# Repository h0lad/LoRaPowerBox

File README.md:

## What is this thing?

This PCB integrates a Heltec HT-CT62 (ESP32-C3 + SX1262), a TI BQ25628E wide-range Li-ion charger and a TI TPS631000 buck-boost converter providing a stable 3.3V rail at up to 1.5A. The TI BQ25628E is capable of handling highly dynamic sources like solar cells and wind generators.

## Features

- 3.9-18V input range, with survival up to 26 V  
- Up to 3.2A input current (IBUS)  
- Up to 2A battery charge current (IBAT)  
- Up to 3.5A system output current (ISW), limited to 1.5A @ 3.3V by the TPS631000  
- Configurable hot/cold charging profile to restrict charging at extreme temperatures  
- Integrated ADC provides full voltage / current telemetry via I²C  
- Pseudo-MPPT (VINDPM + IINDPM) for improved energy harvesting from solar/wind/etc. sources
- Full protection circuitry, allowing operation even with unprotected LiPo cells  
- Reset IC (DI APX803L05) constantly monitors the battery voltage and switches off the 3.3V rail if it reaches a critical level - but keeps the charger always alive

You can see this project as a successor of the [SolarMeshtasticNode](https://github.com/h0lad/SolarMeshtasticNode) project which was a reliable work horse - but showed several limitations. 
Improvements:  

- No voltage dividers required - all measurements available via I²C from the charge controller
- No LED driver transistors needed
- Buck-architecture replaces inefficient LDO regulation
- Significantly improved access to interfaces

## Physical Outlines

The size of the PCB is 60mm x 51mm and is planned (= screw hole fits into housing) around following [Box (120x90x70)](https://de.aliexpress.com/item/1005005859929902.html). 

Do not use the transparent version: it will heat up.

**Simulation of the EdgeCut with a 1:1 print**

## Hardware Verification v0.2

✅ Charging IC charges LiPo and blinks LED according to status

✅ Buck-Boost DCDC creates 3.3V

✅ Heating the thermistor forces throtteling of charging current

✅ Reset IC disables 3.3V using EN pin from DCDC if VBat falls below 3.2V

## FAQ

#### Why are you using a ESP32C3? 

I also do a lot of data gathering into TSDBs via Wifi. The Espressif has the most comfortable stack for doing this.

#### What pins does the LoRa module consume?

The Semtech SX1262 consumes a significant number of GPIOs.

Available pins If LoRa is being used: GPIO0, GPIO1, GPIO18, GPIO19, GPIO20, GPIO21

Note that GPIO8 and GPIO9 are strapping pins and are sampled during early boot.

If the SX1262 is not used, it can be disabled via its CS line (GPIO8) from application code.

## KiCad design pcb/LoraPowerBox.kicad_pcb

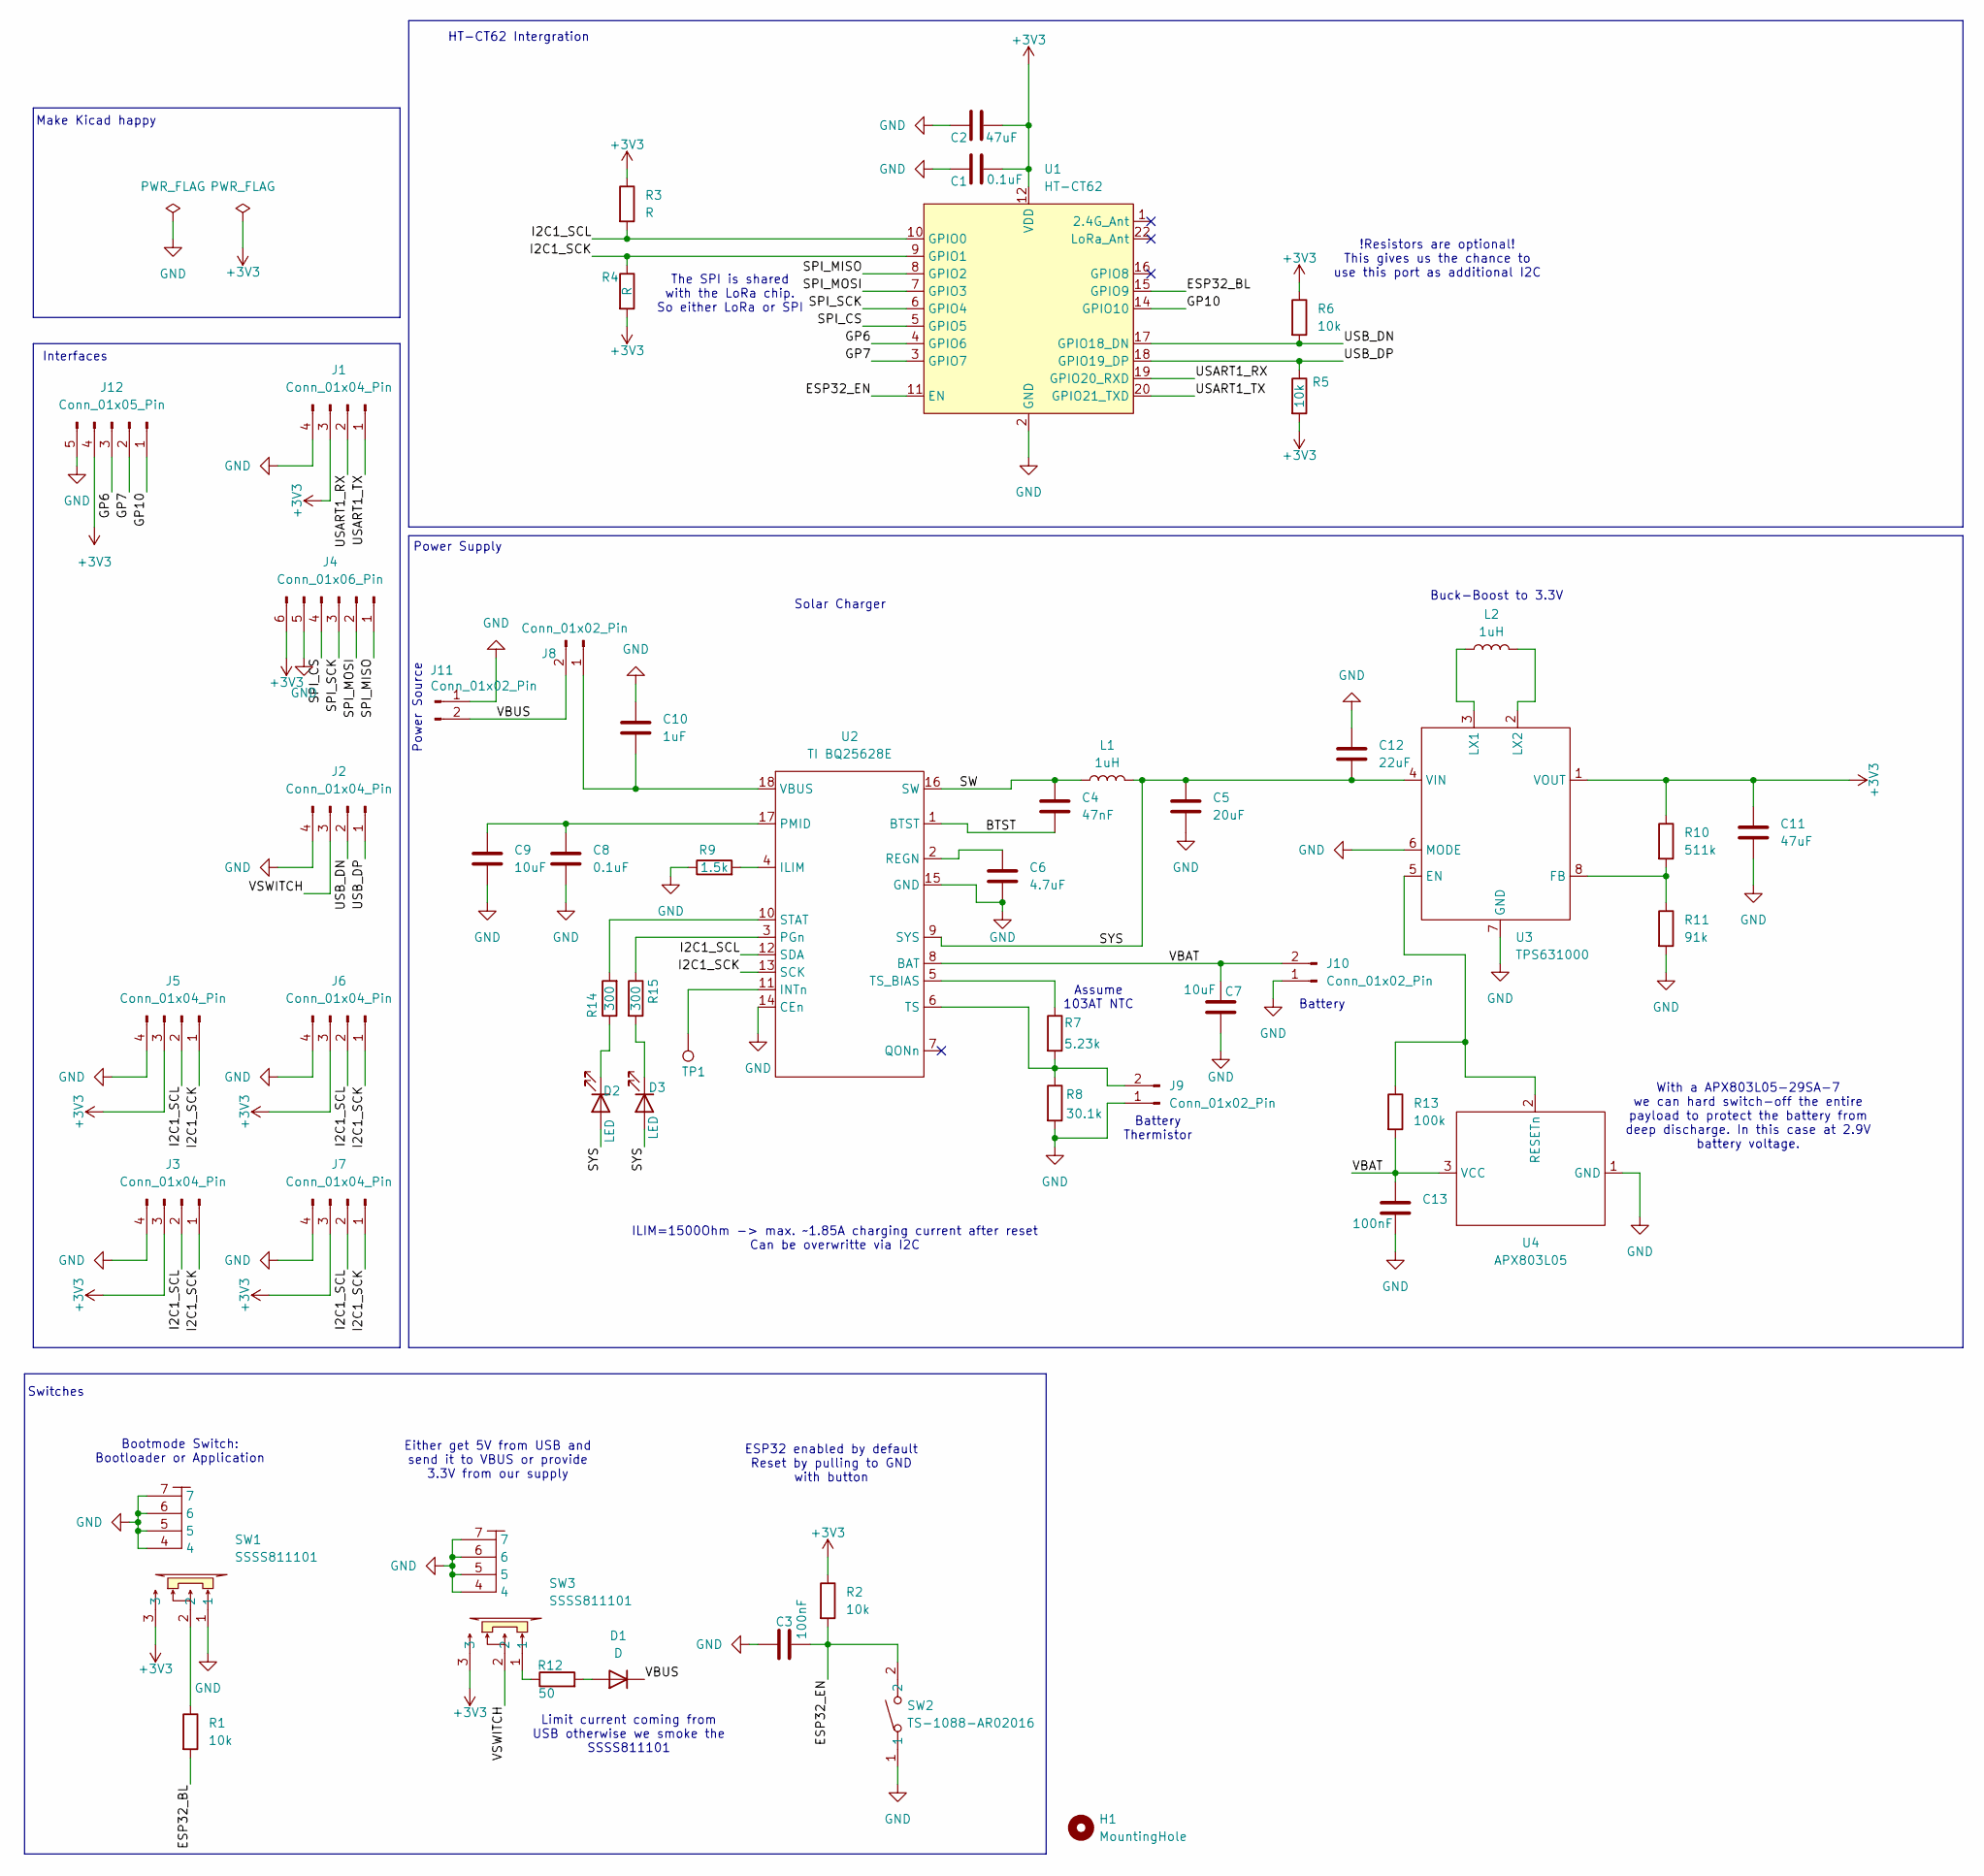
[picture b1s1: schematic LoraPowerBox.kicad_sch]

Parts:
C1, C8: 0.1uF; C_0603_1608Metric_Pad1.08x0.95mm_HandSolder
C2: 47uF; R_1206_3216Metric_Pad1.30x1.75mm_HandSolder
C3, C13: 100nF; C_0603_1608Metric_Pad1.08x0.95mm_HandSolder
C4: 47nF; C_0603_1608Metric_Pad1.08x0.95mm_HandSolder
C5: 20uF; C_0603_1608Metric_Pad1.08x0.95mm_HandSolder
C6: 4.7uF; C_0603_1608Metric_Pad1.08x0.95mm_HandSolder
C7, C9: 10uF; C_0603_1608Metric_Pad1.08x0.95mm_HandSolder
C10: 1uF; C_0603_1608Metric_Pad1.08x0.95mm_HandSolder
C11: 47uF; C_0603_1608Metric_Pad1.08x0.95mm_HandSolder
C12: 22uF; C_0603_1608Metric_Pad1.08x0.95mm_HandSolder
D1: D; D_SOD-323_HandSoldering
D2, D3: LED; LED_0805_2012Metric_Pad1.15x1.40mm_HandSolder
H1: MountingHole; MountingHole_4.3mm_M4_DIN965
J1, J2, J3, J5, J6, J7: Conn_01x04_Pin; JST_PH_B4B-PH-K_1x04_P2.00mm_Vertical
J4: Conn_01x06_Pin; JST_PH_B6B-PH-K_1x06_P2.00mm_Vertical
J8: Conn_01x02_Pin; PinHeader_1x02_P2.54mm_Vertical
J9, J10, J11: Conn_01x02_Pin; JST_PH_B2B-PH-K_1x02_P2.00mm_Vertical
J12: Conn_01x05_Pin; JST_PH_B5B-PH-K_1x05_P2.00mm_Vertical
L1, L2: 1uH; L_1008_2520Metric_Pad1.43x2.20mm_HandSolder
R1, R2, R5, R6: 10k; R_0603_1608Metric_Pad0.98x0.95mm_HandSolder
R3, R4: R; R_0603_1608Metric_Pad0.98x0.95mm_HandSolder
R7: 5.23k; R_0603_1608Metric_Pad0.98x0.95mm_HandSolder
R8: 30.1k; R_0603_1608Metric_Pad0.98x0.95mm_HandSolder
R9: 1.5k; R_0603_1608Metric_Pad0.98x0.95mm_HandSolder
R10: 511k; R_0603_1608Metric_Pad0.98x0.95mm_HandSolder
R11: 91k; R_0603_1608Metric_Pad0.98x0.95mm_HandSolder
R12: 50; R_0603_1608Metric_Pad0.98x0.95mm_HandSolder
R13: 100k; C_0603_1608Metric_Pad1.08x0.95mm_HandSolder
R14, R15: 300; R_0603_1608Metric_Pad0.98x0.95mm_HandSolder
SW1, SW3: SSSS811101; SW-SMD_SSSS811101; LCSC Part C109335
SW2: TS-1088-AR02016; SW-SMD_L3.9-W3.0-P4.45; LCSC Part C720477
TP1: TestPoint; TestPoint_Pad_D1.0mm
U1: HT-CT62; Heltec_HT-CT62
U2: TI BQ25628E; BQ25622ERYKR
U3: TPS631000; SOT-583-8
U4: APX803L05; SOT-23_Handsoldering

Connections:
+3V3: C1.2, C2.2, C11.1, J1.3, J3.3, J4.6, J5.3, J6.3, J7.3, J12.4, R2.1, R3.1, R4.2, R5.2, R6.1, R10.1, SW1.3, SW3.3, U1.12 (VDD), U3.1 (VOUT)
/BTST: C4.1, U2.1 (BTST)
/ESP32_BL: R1.2, U1.15 (GPIO9)
/ESP32_EN: C3.2, R2.2, SW2.2, U1.11 (EN)
/GP6: J12.3, U1.4 (GPIO6)
/GP7: J12.2, U1.3 (GPIO7)
/GP10: J12.1, U1.14 (GPIO10)
/I2C1_SCK: J3.1, J5.1, J6.1, J7.1, R4.1, U1.9 (GPIO1), U2.13 (SCK)
/I2C1_SCL: J3.2, J5.2, J6.2, J7.2, R3.2, U1.10 (GPIO0), U2.12 (SDA)
/SPI_CS: J4.4, U1.5 (GPIO5)
/SPI_MISO: J4.1, U1.8 (GPIO2)
/SPI_MOSI: J4.2, U1.7 (GPIO3)
/SPI_SCK: J4.3, U1.6 (GPIO4)
/SW: C4.2, L1.1, U2.16 (SW)
/SYS: C5.2, C12.2, D2.2 (A), D3.2 (A), L1.2, U2.9 (SYS), U3.4 (VIN)
/USART1_RX: J1.2, U1.19 (GPIO20_RXD)
/USART1_TX: J1.1, U1.20 (GPIO21_TXD)
/USB_DN: J2.2, R6.2, U1.17 (GPIO18_DN)
/USB_DP: J2.1, R5.1, U1.18 (GPIO19_DP)
/VBAT: C7.2, C13.2, J10.2, R13.2, U2.8 (BAT), U4.3 (VCC)
/VBUS: D1.1 (K), J8.2, J11.2
/VSWITCH: J2.3, SW3.2
GND: C1.1, C2.1, C3.1, C5.1, C6.1, C7.1, C8.1, C9.1, C10.2, C11.2, C12.1, C13.1, J1.4, J2.4, J3.4, J4.5, J5.4, J6.4, J7.4, J9.1, J10.1, J11.1, J12.5, R8.2, R9.1, R11.2, SW1.1, SW1.4, SW1.5, SW1.6, SW1.7, SW2.1, SW3.4, SW3.5, SW3.6, SW3.7, U1.2 (GND), U1.13 (GND), U1.21 (GND), U2.14 (CEn), U2.15 (GND), U3.6 (MODE), U3.7 (GND), U4.1 (GND)
unnamed: D1.2 (A), R12.2
unnamed: D2.1 (K), R14.1
unnamed: D3.1 (K), R15.2
unnamed: C10.1, J8.1, U2.18 (VBUS)
unnamed: J9.2, R7.2, R8.1, U2.6 (TS)
unnamed: R1.1, SW1.2
unnamed: R12.1, SW3.1
unnamed: R9.2, U2.4 (ILIM)
unnamed: TP1.1 (1_1), U2.11 (INTn)
unnamed: R15.1, U2.3 (PGn)
unnamed: C8.2, C9.2, U2.17 (PMID)
unnamed: C6.2, U2.2 (REGN)
unnamed: R14.2, U2.10 (STAT)
unnamed: R7.1, U2.5 (TS_BIAS)
unnamed: R13.1, U3.5 (EN), U4.2 (RESETn)
unnamed: R10.2, R11.1, U3.8 (FB)
unnamed: L2.1, U3.3 (LX1)
unnamed: L2.2, U3.2 (LX2)

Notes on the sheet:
ILIM=1500Ohm -> max. ~1.85A charging current after reset Can be overwritte via I2C
!Resistors are optional! This gives us the chance to use this port as additional I2C
The SPI is shared with the LoRa chip. So either LoRa or SPI
With a APX803L05-29SA-7 we can hard switch-off the entire payload to protect the battery from deep discharge. In this case at 2.9V battery voltage.
Power Source
HT-CT62 Intergration
Battery Thermistor
Power Supply
Bootmode Switch: Bootloader or Application
Buck-Boost to 3.3V
Limit current coming from USB otherwise we smoke the SSSS811101
Assume 103AT NTC
Battery
Interfaces
ESP32 enabled by default Reset by pulling to GND with button
Make Kicad happy
Either get 5V from USB and send it to VBUS or provide 3.3V from our supply
Switches
Solar Charger

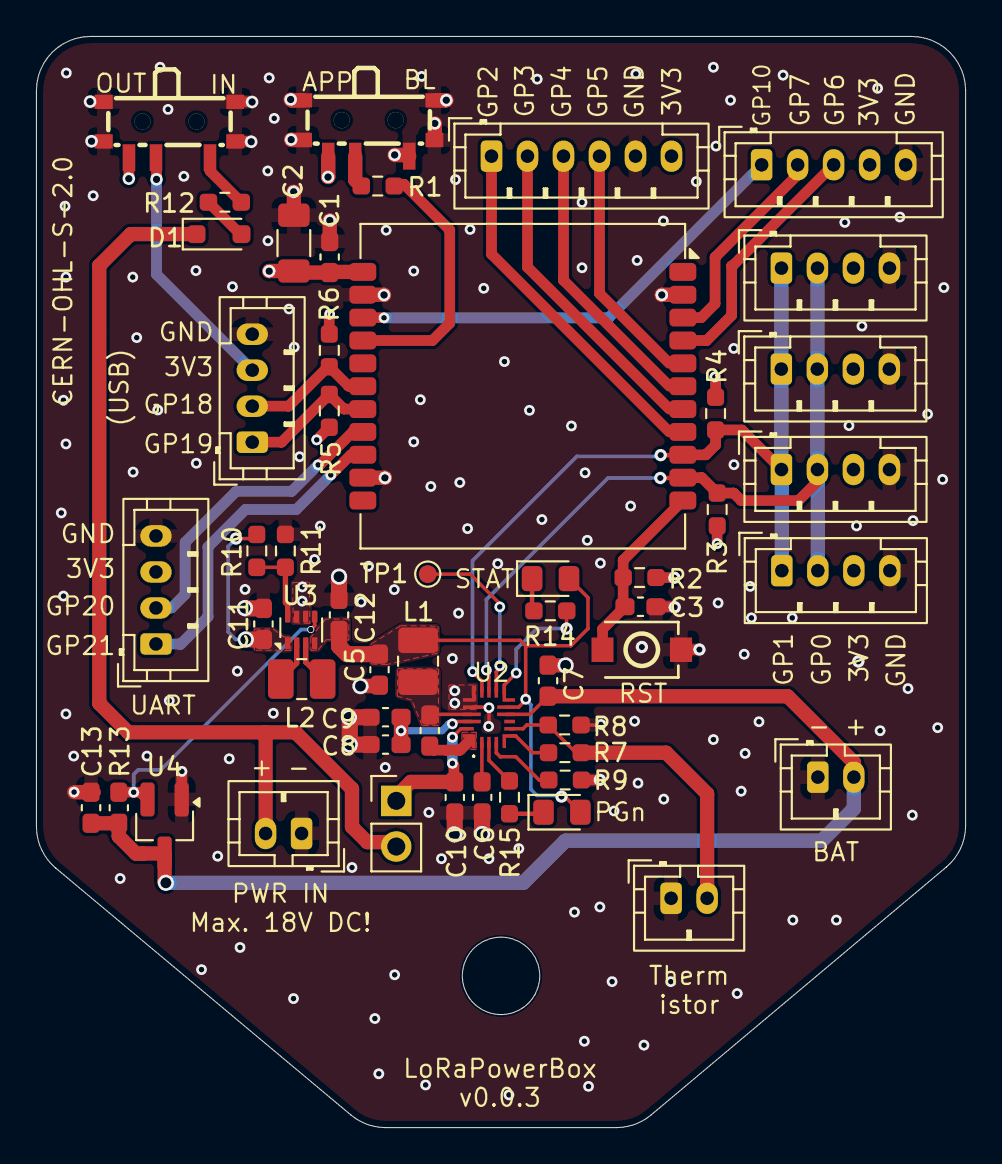
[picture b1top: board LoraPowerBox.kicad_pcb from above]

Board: 4 copper layers, 51.6 x 60.6 mm, 54 parts (0 on the bottom side), 41 nets.

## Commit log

2025-12-28 doc: replace wrong picture
2025-12-29 pcb: reduce edge cut size a bit
2025-12-29 pcb: missed to fillet an edge
2025-12-29 README: spelling
2025-12-29 pcb, sch: expose interrupt pin of charge controller to test pad
2025-12-29 pcb: make it a little bit more symmetric
2025-12-29 README: add missing dot
2025-12-29 pcb: non-functional clean ups
2025-12-29 pcb: fix another symmetry issue
2025-12-29 pcb: add a few more vias to gnd
2025-12-30 README: it's not only solar - remove it
2025-12-30 README: add informations regarding physical outlines
2026-01-02 pcb, doc: move PWR IN a little bit to the left
2026-01-02 pcb, doc: opimize some silk prints
2026-01-02 pcb, sch: add resistor values for NTC voltage divider
2026-01-03 README: only Buck - no Boost
2026-01-03 README: be more precise about mounting hole
2026-01-03 README: add picture of box
2026-01-03 docs: resize picture size a bit
2026-01-03 README: explain picture
2026-01-04 pcb, sch: replace M3 hounting hole with M4
2026-01-04 README: move text blocks around
2026-01-04 README: reduce text duplication
2026-01-04 pcb: the internal ADC maxes out at 18V. So rework silk print regaring voltage limits
2026-01-04 pcb: finally found the right kicad buttoms to center everything correctly
2026-01-05 README: add warning
2026-01-05 sch, pcb: add reset IC that monitors the battery for us
    The BQ25628 has a UVLO (Battery Undervoltage Lockout) protection which
    is very very low (configurable voltages <2.5).
    Add an additional battery monitor which allows us to automatically
    switch off the 3.3V coming from the Buck-/Boost-Converter but keeps the
    BQ25628 alive so it can recharge the battery.
2026-01-05 pcb: eye candy - move reset ic a little bit to the left
2026-01-05 README: add reset ic feature
2026-01-05 README: fix typo
2026-01-26 README: add FAQ
2026-02-09 README: add hardware verification results
2026-02-09 README: tested v0.2
2026-02-10 README: merge chapter
2026-04-10 prj, pcb, sch: update to Kicad10
2026-04-10 pcb, sch: add a resistor to the LEDs

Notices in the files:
pcb/LoraPowerBox.kicad_pcb:
CERN-OHL-S-2.0
